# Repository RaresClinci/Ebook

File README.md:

# Openbook E-Reader

## Schema bloc
``` mermaid
 flowchart TB
    USB1["USB-C"] -->|5V| Charger1["Battery Charger (MCP73832)"]
    Charger1 -->|Charging| LiPo1["LiPo Battery"]
    LiPo1 --> LDO1["3V3 LDO"]
    LiPo1 --> DC5["5V DC/DC"]

    ESP1["ESP32-C3-WROOM"]

    LDO1 -->|3.3V| ESP1
    LDO1 -->|3.3V| Display1["1.5'' E-Ink Display (200x200px)"]
    LDO1 -->|3.3V| SD1["SD Card"]
    LDO1 -->|3.3V| Temp1["Temp/RH Sensor (BME680)"]
    LDO1 -->|3.3V| BatteryGauge["Battery Fuel Gauge (MAX17048)"]
    LDO1 -->|3.3V| Buttons1["Buttons (3x)"]

    ESP1 -- SPI --> Display1
    ESP1 -- SPI --> SD1
    ESP1 -- GPIO --> Buttons1
    ESP1 -- I2C --> Temp1
    ESP1 -- I2C --> BatteryGauge
    ESP1 -- I2C --> RTC["Real Time Clock (DS3231)"]
    ESP1 -- USB --> USB1

```

## Bill of Materials

Pentru componentele care se repeta, am adaugat doar la prima aparitioe datasheetul si linkul catre site.
TP-urile le-am proiectat singur, de aceea nu au o datasheet si un link catre site.

| Name of component  | Device                                    | Check Prices                                                                 | DataSheet                                                                  |
|--------------------|-------------------------------------------|-----------------------------------------------------------------------------|----------------------------------------------------------------------------|
| BOOT_BUTTON        | BUTTON_CUSYOMV1                           | [Check Price](https://industry.panasonic.com/global/en/products/control/switch/light-touch/number/evqpuj02k)  | [DataSheet](https://industry.panasonic.com/global/en/products/control/switch/light-touch/number/evqpuj02k) |
| C1                 | ESP32_WROVER_EAGLE-LTSPICE_CC0402         | [Check Price](https://industry.panasonic.com/global/en/products/control/switch/light-touch/number/evqpuj02k)  | [DataSheet](https://industry.panasonic.com/global/en/products/control/switch/light-touch/number/evqpuj02k) |
| C1_BAT             | ESP32_WROVER_EAGLE-LTSPICE_CC0402         | #N/A                                                                         | #N/A                                                                      |
| C1_BAT1            | EAGLE-LTSPICE_CC0402                      | #N/A                                                                         | #N/A                                                                      |
| C1_BAT2            | EAGLE-LTSPICE_CC0402                      | #N/A                                                                         | #N/A                                                                      |
| C2                 | ESP32_WROVER_EAGLE-LTSPICE_CC0402         | #N/A                                                                         | #N/A                                                                      |
| C2_BAT           | ESP32_WROVER_EAGLE-LTSPICE_CC0402         | #N/A                                                                         | #N/A                                                                      |
| C3                 | RCL_CPOL-EUCT3528                         | #N/A                                                                         | #N/A                                                                      |
| C4                 | ESP32_WROVER_EAGLE-LTSPICE_CC0402         | #N/A                                                                         | #N/A                                                                      |
| C4_USB             | ESP32_WROVER_EAGLE-LTSPICE_CC0402         | #N/A                                                                         | #N/A                                                                      |
| C5                 | ESP32_WROVER_EAGLE-LTSPICE_CC0402         | #N/A                                                                         | #N/A                                                                      |
| C5_USB             | ESP32_WROVER_EAGLE-LTSPICE_CC0402         | #N/A                                                                         | #N/A                                                                      |
| C6                 | ESP32_WROVER_EAGLE-LTSPICE_CC0402         | #N/A                                                                         | #N/A                                                                      |
| C7                 | ESP32_WROVER_EAGLE-LTSPICE_CC0402         | #N/A                                                                         | #N/A                                                                      |
| C8                 | ESP32_WROVER_EAGLE-LTSPICE_CC0402         | #N/A                                                                         | #N/A                                                                      |
| C9                 | EAGLE-LTSPICE_CC0402                      | #N/A                                                                         | #N/A                                                                      |
| C10                | ESP32_WROVER_EAGLE-LTSPICE_CC0402         | #N/A                                                                         | #N/A                                                                      |
| C10_SUPERCAP       | CPH3225A                                  | [Check Price](https://www.snapeda.com/parts/CPH3225A/Seiko+Instruments/view-part/?ref=eda) | [DataSheet](https://www.snapeda.com/parts/CPH3225A/Seiko+Instruments/view-part/?ref=eda) |
| CHANGE_BUTTON      | BUTTON_CUSYOMV1                           | [Check Price](https://industry.panasonic.com/global/en/products/control/switch-light-touch/number/evqpuj02k)  | [DataSheet](https://industry.panasonic.com/global/en/products/control/switch-light-touch/number/evqpuj02k) |
| CHG_LED            | ADAFRUIT_LEDCHIP-LED0603                  | [Check Price](https://www.snapeda.com/parts/KP-1608SURCK/Kingbright/view-part/?ref=search&t=LED%200603) | [DataSheet](https://www.snapeda.com/parts/KP-1608SURCK/Kingbright/view-part/?ref=search&t=LED%200603) |
| C_DELAY            | ESP32_WROVER_EAGLE-LTSPICE_CC0402         | #N/A                                                                         | #N/A                                                                      |
| D1                 | USBLC6-2SC6Y                              | [Check Price](https://www.snapeda.com/parts/USBLC6-2SC6Y/STMicroelectronics/view-part/?ref=eda) | [DataSheet](https://www.snapeda.com/parts/USBLC6-2SC6Y/STMicroelectronics/view-part/?ref=eda) |
| D2                 | ESP32_WROVER_AVX---SD0805S020S1R0_AVX_... | [Check Price](https://eu.mouser.com/ProductDetail/KYOCERA-AVX/SD0805S020S1R0?qs=jCA%252BPfw4LHbpkAoSnwrdjw%3D%3D) | [DataSheet](http://datasheets.avx.com/schottky.pdf)                       |
| D3                 | MBR0530                                   | [Check Price](https://eu.mouser.com/ProductDetail/KYOCERA-AVX/SD0805S020S1R0?qs=jCA%252BPfw4LHbpkAoSnwrdjw%3D%3D) | [DataSheet](https://eu.mouser.com/ProductDetail/KYOCERA-AVX/SD0805S020S1R0?qs=jCA%252BPfw4LHbpkAoSnwrdjw%3D%3D) |
| D4                 | MBR0530                                   | [Check Price](https://www.snapeda.com/parts/MBR0530/Onsemi/view-part/?ref=eda) | [DataSheet](https://www.snapeda.com/parts/MBR0530/Onsemi/view-part/?ref=eda) |
| D5                 | MBR0530                                   | [Check Price](https://www.snapeda.com/parts/MBR0530/Onsemi/view-part/?ref=eda) | [DataSheet](https://www.snapeda.com/parts/MBR0530/Onsemi/view-part/?ref=eda) |
| D6                 | PGB1010603MR                              | [Check Price](https://www.snapeda.com/parts/PGB1010603MR/Littelfuse/view-part/?ref=eda) | [DataSheet](https://www.snapeda.com/parts/PGB1010603MR/Littelfuse/view-part/?ref=eda) |
| D7                 | ESP32_WROVER_AVX---SD0805S020S1R0_AVX_... | [Check Price](https://eu.mouser.com/ProductDetail/KYOCERA-AVX/SD0805S020S1R0?qs=jCA%252BPfw4LHbpkAoSnwrdjw%3D%3D) | [DataSheet](http://datasheets.avx.com/schottky.pdf)                       |
| D8                 | PGB1010603MR                              | [Check Price](https://www.snapeda.com/parts/PGB1010603MR/Littelfuse/view-part/?ref=eda) | [DataSheet](https://www.snapeda.com/parts/PGB1010603MR/Littelfuse/view-part/?ref=eda) |
| D9                 | PGB1010603MR                              | [Check Price](https://www.snapeda.com/parts/PGB1010603MR/Littelfuse/view-part/?ref=eda) | [DataSheet](https://www.snapeda.com/parts/PGB1010603MR/Littelfuse/view-part/?ref=eda) |
| D10                | PGB1010603MR                              | [Check Price](https://www.snapeda.com/parts/PGB1010603MR/Littelfuse/view-part/?ref=eda) | [DataSheet](https://www.snapeda.com/parts/PGB1010603MR/Littelfuse/view-part/?ref=eda) |
| D11                | PGB1010603MR                              | [Check Price](https://www.snapeda.com/parts/PGB1010603MR/Littelfuse/view-part/?ref=eda) | [DataSheet](https://www.snapeda.com/parts/PGB1010603MR/Littelfuse/view-part/?ref=eda) |
| D12                | PGB1010603MR                              | [Check Price](https://www.snapeda.com/parts/PGB1010603MR/Littelfuse/view-part/?ref=eda) | [DataSheet](https://www.snapeda.com/parts/PGB1010603MR/Littelfuse/view-part/?ref=eda) |
| EPD_C1             | ESP32_WROVER_EAGLE-LTSPICE_CC0402         | #N/A                                                                         | #N/A                                                                      |
| EPD_C2             | ESP32_WROVER_EAGLE-LTSPICE_CC0402         | #N/A                                                                         | #N/A                                                                      |
| EPD_C5             | ESP32_WROVER_EAGLE-LTSPICE_CC0402         | #N/A                                                                         | #N/A                                                                      |
| EPD_C6             | ESP32_WROVER_EAGLE-LTSPICE_CC0402         | #N/A                                                                         | #N/A                                                                      |
| EPD_C7             | ESP32_WROVER_EAGLE-LTSPICE_CC0402         | #N/A                                                                         | #N/A                                                                      |
| EPD_C8             | ESP32_WROVER_EAGLE-LTSPICE_CC0402         | #N/A                                                                         | #N/A                                                                      |
| EPD_C9             | ESP32_WROVER_EAGLE-LTSPICE_CC0402         | #N/A                                                                         | #N/A                                                                      |
| EPD_C10            | ESP32_WROVER_EAGLE-LTSPICE_CC0402         | #N/A                                                                         | #N/A                                                                      |
| EPD_C11            | ESP32_WROVER_EAGLE-LTSPICE_CC0402         | #N/A                                                                         | #N/A                                                                      |
| EPD_C12            | ESP32_WROVER_EAGLE-LTSPICE_CC0402         | #N/A                                                                         | #N/A                                                                      |
| IC1                | BD5229G-TR                                | [Check Price](https://componentsearchengine.com/part-view/BD5229G-TR/ROHM%20Semiconductor) | [DataSheet](https://componentsearchengine.com/part-view/BD5229G-TR/ROHM%20Semiconductor) |
| IC4                | XC6220A331MR-G                            | [Check Price](https://componentsearchengine.com/part-view/XC6220A331MR-G/Torex) | [DataSheet](https://componentsearchengine.com/part-view/XC6220A331MR-G/Torex) |
| J1                 | FH34SRJ-24S-0.5SH_99_                     | [Check Price](https://componentsearchengine.com/part-view/XC6220A331MR-G/Torex) | [DataSheet](https://componentsearchengine.com/part-view/XC6220A331MR-G/Torex) |
| J2                 | SAMACSYS_PARTS_USB4110-GF-A               | [Check Price](https://componentsearchengine.com/part-view/USB4110-GF-A/GCT%20(GLOBAL%20CONNECTOR%20TECHNOLOGY) | [DataSheet](https://componentsearchengine.com/part-view/USB4110-GF-A/GCT%20(GLOBAL%20CONNECTOR%20TECHNOLOGY) |
| J3                 | QWIIC_CONNECTORJS-1MM                     | [Check Price](https://www.snapeda.com/parts/PRT-14417/SparkFun%20Electronics/view-part/?ref=search&t=qwiic%20connectpr)                                                                         | [Datasheet](https://www.snapeda.com/parts/PRT-14417/SparkFun%20Electronics/view-part/?ref=search&t=qwiic%20connectpr)                                                                        |
| J4                 | 112A-TAAR-R03_ATTEND                      | [Check Price](https://store.comet.srl.ro/Catalogue/Product/43497/)           | [DataSheet](https://store.comet.srl.ro/Catalogue/Product/43497/)          |
| L1                 | 744043680IND_4828-WE-TPC_WRE              | [Check Price](https://eu.mouser.com/ProductDetail/Wurth-Elektronik/744043680?qs=PGXP4M47uW6VkZq%252BkzjrHA%3D%3D) | [DataSheet](https://eu.mouser.com/ProductDetail/Wurth-Elektronik/744043680?qs=PGXP4M47uW6VkZq%252BkzjrHA%3D%3D) |
| PFMF.050.1         | ESP32C6_VARISTORCN1812                    | [Check Price](https://www.mouser.co.uk/ProductDetail/EPCOS-TDK/B72520T0350K062?qs=dEfas%2FXlABIszF52uu7vrg%3D%3D) | [DataSheet](https://www.mouser.co.uk/ProductDetail/EPCOS-TDK/B72520T0350K062?qs=dEfas%2FXlABIszF52uu7vrg%3D%3D) |
| Q1                 | ESP32_WROVER_SPARKFUN-DISCRETESEMI_MOSFET_... | [Check Price](https://componentsearchengine.com/part-view/DMG2305UX-7/Diodes%20Incorporated) | [DataSheet](https://componentsearchengine.com/part-view/DMG2305UX-7/Diodes%20Incorporated) |
| Q2                 | ESP32_WROVER_SPARKFUN-DISCRETESEMI_MOSFET_... | #N/A                                                                         | #N/A                                                                      |
| Q3                 | D8                                        | [Check Price](https://componentsearchengine.com/part-view/PGB1010603MR/Littelfuse) | [DataSheet](https://componentsearchengine.com/part-view/PGB1010603MR/Littelfuse) |
| Q4                 | Q2_TS-B2_REACHPACK                        | #N/A                                                                         | #N/A                                                                      |
| SJ1                 | SJ                                        | [Check Price](https://grabcad.com/library/solder-jumpers-1) | [DataSheet](https://grabcad.com/library/solder-jumpers-1) |                                                                  |

## Descriere detaliată a funcționalității hardware

### 1. Microcontroller – ESP32-C6
Dispozitivul se bazează pe microcontroller-ul**ESP32-C6-WROOM-1**, bazat pe un nucleu **RISC-V pe 32 de biți**, cu frecvențe de lucru de până la **160 MHz**.

- **Memorie**: 512 KB de SRAM intern și **8 MB flash extern** (W25Q512JVEIQ).
- **Conectivitate**: Wi-Fi 6, Bluetooth 5 LE, USB 2.0
- **Periferice**: suport pentru SPI, I²C, UART și multiple GPIO-uri.
- **Moduri de consum redus**: suportă sleep și deep sleep, ideale pentru dispozitive portabile alimentate cu baterie.

### 2. Afișaj E-Ink
**E-Ink de 7.5" (800x480px)** – Waveshare (sau echivalent) cu rezoluție 800×480

**Interfață**: 4-wire SPI + pini de control (CS, DC, RST, BUSY).  
**Consum**: extrem de redus în regim static; doar în timpul reîmprospătării imaginea consumul crește la ~15–25mA.

 **Avantaj**: Afișajele E-Ink păstrează imaginea fără consum de curent, ceea ce le face perfecte pentru aplicații de tip e-reader.

### 3. Senzor de Mediu – BME680
Senzorul integrează măsurători de **temperatură**, **umiditate**, **presiune atmosferică** și **calitate a aerului (VOC/eCO₂)**.

- **Interfață**: I²C la 400 kHz.
- **Consum**: ~2.1µA în standby, până la câțiva mA în timpul citirilor.

 **BME680** este o alegere excelenta datorita capacitatii sale de a integra multiple tipuri de masuratori intr-un singur cip

### 4. Managementul energiei
- **Baterie Li-Po 3.7V, 2500mAh** – oferă autonomie extinsă.
- **Circuit de încărcare**: MCP73831, conectat la USB-C, permite încărcare cu până la **1A**.
- **Fuel Gauge**: MAX17048 – monitorizează starea bateriei prin I²C (tensiune, încărcare, alertă descărcare).
- **LDO**: XC6220A331MR-G – asigură **tensiune stabilă de 3.3V** pentru toate componentele critice.

### 5. Interacțiune – Butoane (3x)
Dispozitivul include **trei butoane tactile** pentru navigare, selectare și întoarcere pagină. Fiecare este conectat la un GPIO și poate avea debouncing hardware (rezistor + condensator) sau software, pentru evitarea semnalelor false.

### 6. Port USB-C
- **Roluri**: încărcarea bateriei, transfer de date (USB 2.0), și update de firmware (via bootloader sau OTA).
- **Protecție**: ESD (ex: USBLC6-2SC6Y), rezistențe de terminare conforme cu specificațiile USB-C.

### 7. Conector Qwiic (I²C)
Conector standard cu 4 pini (VCC, GND, SDA, SCL) pentru atașarea rapidă a senzorilor/modulor I²C, ideal în extensii și prototipare.

### 8. Card MicroSD(112A-TAAR-R03)
- **Conector dedicat**: pentru log-uri, e-book-uri sau update-uri firmware.
- **Interfață**: Poate fi SD (1-bit / 4-bit) sau SPI, în funcție de configurația firmware-ului.

### 9. Ceas de timp real – RTC DS3231
- **Precizie ridicată**.
- **Backup**: cu baterie sau supercondensator.
- **Comunicare**: I²C, împreună cu ceilalți senzori.

### 10. Memorie Flash externă – W25Q512JVEIQ
- **Interfață**: quad SPI – pentru încărcare rapidă de date și firmware.
- Utilizată pentru stocarea aplicațiilor, imaginilor sau fișierelor mari (ex: e-book-uri).

---

### Interfețele utilizate

| Interfață | Componente conectate |
|----------|------------------------|
| **SPI**  | Afișaj E-Ink, memorie flash externă, card SD |
| **I²C**  | BME680, MAX17048 (fuel gauge), RTC DS3231, conector Qwiic |
| **GPIO** | Butoane, control display (RST, BUSY etc.) |
| **USB**  | Alimentare și date (USB-C) |

---

### Estimare consum energetic

| Componentă              | Consum tipic                     |
|-------------------------|----------------------------------|
| ESP32 (activ)           | ~80 mA (Wi-Fi) / <10 mA (idle)   |
| E-Ink (refresh)         | ~15–25 mA                        |
| BME680                  | ~3.6 mA (peak) / 2.1 µA (sleep)  |
| MAX17048 (Fuel Gauge)   | ~50 µA                           |
| DS3231 (RTC)            | ~3.5 mA (activ) / <1 µA (backup) |
| Total (deep sleep)      | ~50–100 µA                       |
| Total (activ cu Wi-Fi)  | ~100–150 mA                      |

> Cu o baterie de **2500mAh**, în regim normal de utilizare (afișaj static, deep sleep majoritatea timpului), autonomia poate atinge **câteva săptămâni**.

## Alocarea pinilor pentru ESP32-C6

| Pin ESP32-C6  | Componentă / Semnal                       | Descriere                                           |
|---------------|-------------------------------------------|-----------------------------------------------------|
| GPIO1         | I²C SDA (BME680, MAX17048, DS3231, Qwiic) | Linie de date partajată pentru toți senzorii(+ RTC) conectați pe magistrala I²C. |
| GPIO2         | I²C SCL (BME680, MAX17048, DS3231, Qwiic) | Linie de clock pentru sincronizarea comunicației I²C. |
| GPIO5         | SPI MISO (E-Paper)                        | Recepție date de la afișajul E-Paper.              |
| GPIO6         | SPI MOSI (E-Paper)                        | Transmitere date către afișajul E-Paper.           |
| GPIO7         | SPI CLK (E-Paper)                         | Semnal de clock pentru interfața SPI a ecranului.  |
| GPIO8         | SPI CS (E-Paper)                          | Chip Select pentru e-paper.   |
| GPIO9         | E-Paper DC (Data/Command)                 | Selectează între transmiterea de date sau comenzi către afișaj. |
| GPIO10        | E-Paper RST                               | Reset hardware al afișajului.                      |
| GPIO11        | E-Paper BUSY                              | Indică dacă afișajul este ocupat cu o operație.    |
| GPIO12        | Button #1                                 | Buton de control (ex. „Pagina următoare”).         |
| GPIO13        | Button #2                                 | Buton de control (ex. „Pagina anterioară”).        |
| GPIO14        | Button #3                                 | Buton de control (ex. „Meniu” sau „Select”).       |
| GPIO15        | MAX17048 ALERT (opțional)                 | Semnal de alertă de la senzorul de baterie (low battery). |
| GPIO16        | USB D+ (intern la USB PHY)                | Semnal diferențial pozitiv pentru conexiunea USB 2.0. |
| GPIO17        | USB D- (intern la USB PHY)                | Semnal diferențial negativ pentru conexiunea USB 2.0. |
| GPIO18        | LED de status (opțional)                  | LED pentru semnalizare stări (Wi-Fi, încărcare etc.). |
| GPIO19        | SD Card CS (opțional)                     | Chip Select pentru cardul microSD (SPI).           |
| GPIO20        | SD Card MISO (opțional)                   | Linie de citire date de la cardul microSD.         |
| GPIO21        | SD Card MOSI (opțional)                   | Linie de scriere date către cardul microSD.        |
| GPIO4         | SD Card CLK (opțional)                    | Linie de clock pentru comunicația SPI cu cardul SD.|

## Note
- am adaugat la partea de PCB 2D niste masuratori in plus pentru claritate
- am pozitionat TP-urile in cel mai apropiat loc de componentele conectate
- am mai adaugat pe placa o zona unde poate fi scris numarul de serie al placii si versiunea ei(probabil va deveni Openbook v1.2 dupa feedback - UPDATE: chiar a devenit)
- pentru baterie, am folosit un paralelipiped cu dimensiunile maxime din datasheet
- la partea de PCB, am aprobat 2 erori de gauri de la o componenta si o eroare de Airwire la componenta J4, are 9 grounduri puse intr-un grid 3x3 si cel din mijloc nu e accesibil

## Concluzii
A fost un proiect destul de solicitant, dar cu multa munca am reusit sa il duc pana la capat. Am luat in considerare majoritatea indicatiilor si sunt deschis sa fac imbunatatiri pe urma feedbackului.

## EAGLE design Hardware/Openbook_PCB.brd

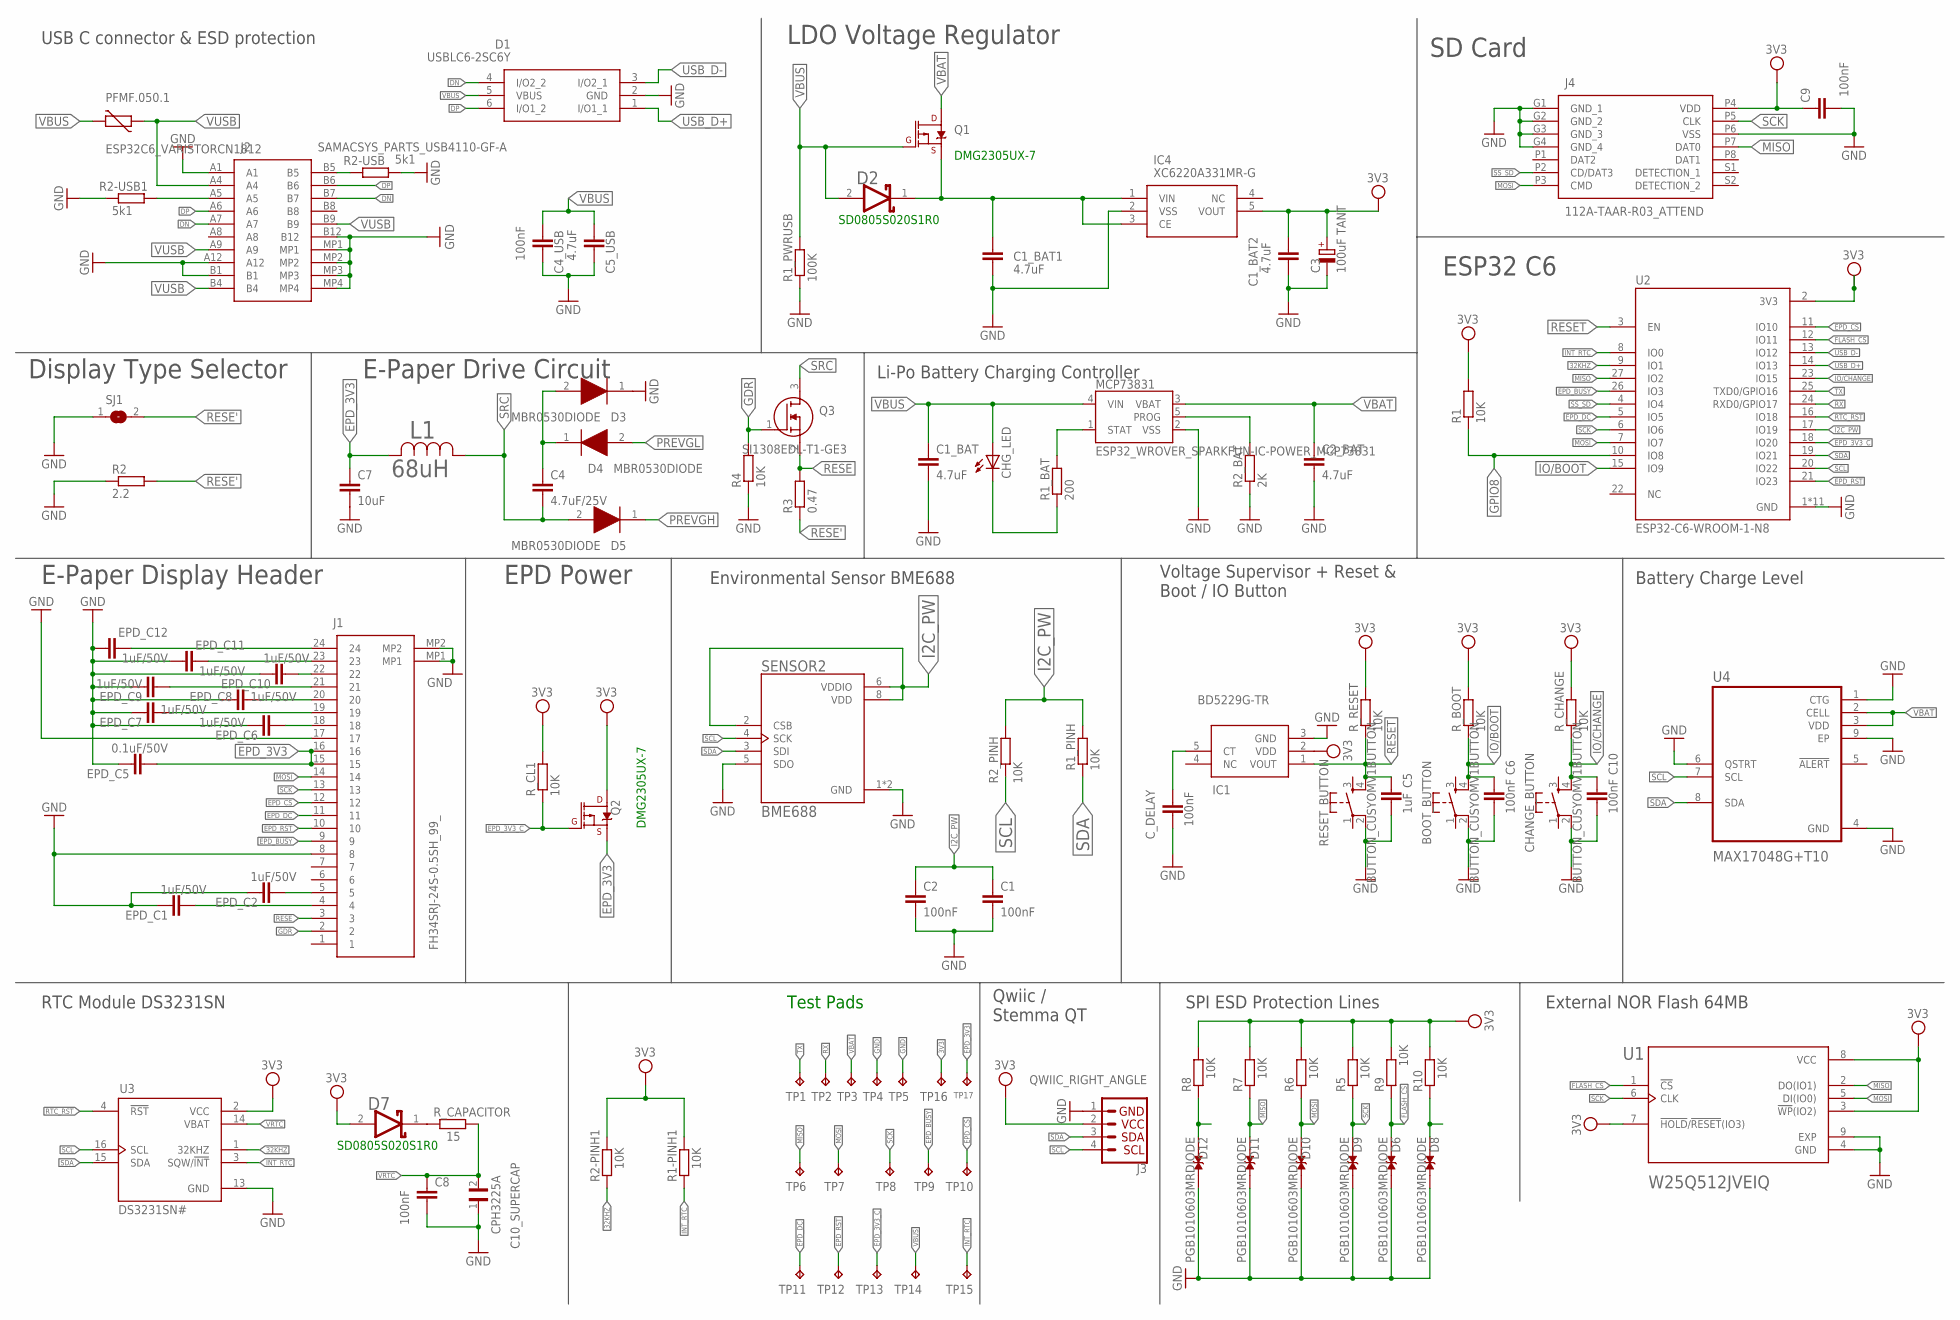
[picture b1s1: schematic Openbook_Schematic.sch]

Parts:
BOOT_BUTTON: BUTTON_CUSYOMV1BUTTON; MYBUTTON
C1, C2, C4_USB, C6, C8, C9, C10: 100nF; EAGLE-LTSPICE_C0402
C1_BAT, C1_BAT1, C1_BAT2, C2_BAT, C5_USB: 4.7uF; EAGLE-LTSPICE_C0402
C3: 100uF TANT; RCL_CT3528
C4: 4.7uF/25V; EAGLE-LTSPICE_C0402
C5: 1uF; EAGLE-LTSPICE_C0402
C7: 10uF; EAGLE-LTSPICE_C0402
C10_SUPERCAP: CPH3225A; CAPCP3225X100N
CHANGE_BUTTON: BUTTON_CUSYOMV1BUTTON; MYBUTTON
CHG_LED: ADAFRUIT_LEDCHIP-LED0603; ADAFRUIT_CHIP-LED0603
C_DELAY: 100nF; EAGLE-LTSPICE_C0402
D1: USBLC6-2SC6Y; SOT95P280X145-6N
D2, D7: SD0805S020S1R0; ESP32_WROVER_AVX---SD0805S020S1R0_AVX_SD0805S020S1R0_0
D3, D4, D5: MBR0530DIODE; SOD3716X135N
D6, D8, D9, D10, D11, D12: PGB1010603MRDIODE; DIOC1608X36N
EPD_C1, EPD_C2, EPD_C6, EPD_C7, EPD_C8, EPD_C9, EPD_C10, EPD_C11, EPD_C12: 1uF/50V; EAGLE-LTSPICE_C0402
EPD_C5: 0.1uF/50V; EAGLE-LTSPICE_C0402
IC1: BD5229G-TR; SOT95P280X125-5N
IC4: XC6220A331MR-G; SOT95P280X120-5N
J1: FH34SRJ-24S-0.5SH_99_; FH34SRJ24S05SH99
J2: SAMACSYS_PARTS_USB4110-GF-A; SAMACSYS_PARTS_USB4110GFA
J3: QWIIC_RIGHT_ANGLE; JST04_1MM_RA
J4: 112A-TAAR-R03_ATTEND; 112ATAARR03ATTEND
L1: 68uH; IND_4828-WE-TPC_WRE
MCP73831: ESP32_WROVER_SPARKFUN-IC-POWER_MCP73831; ESP32_WROVER_SPARKFUN-IC-POWER_SOT23-5
PFMF.050.1: ESP32C6_VARISTORCN1812; ESP32C6_VARISTOR_CT/CN1812
Q1, Q2: 20V/4.2A/52mΩ/1.4W; ESP32_WROVER_SPARKFUN-DISCRETESEMI_SOT23-3
Q3: SI1308EDL-T1-GE3; SOT65P210X110-3N
R1, R1-PINH1, R1_PINH, R2-PINH1, R2_PINH, R4, R5, R6, R7, R8, R9, R10: 10K; ESP32_WROVER_EAGLE-LTSPICE_R0402
R1_BAT: 200; ESP32_WROVER_EAGLE-LTSPICE_R0402
R1_PWRUSB: 100K; ESP32_WROVER_EAGLE-LTSPICE_R0402
R2: 2.2; ESP32_WROVER_EAGLE-LTSPICE_R0402
R2-USB, R2-USB1: 5k1; ESP32_WROVER_EAGLE-LTSPICE_R0402
R2_BAT: 2K; ESP32_WROVER_EAGLE-LTSPICE_R0402
R3: 0.47; ESP32_WROVER_EAGLE-LTSPICE_R0402
RESET_BUTTON: BUTTON_CUSYOMV1BUTTON; MYBUTTON
R_BOOT: 10K; ESP32_WROVER_EAGLE-LTSPICE_R0402
R_CAPACITOR: 15; ESP32_WROVER_EAGLE-LTSPICE_R0402
R_CHANGE: 10K; ESP32_WROVER_EAGLE-LTSPICE_R0402
R_CL1: 10K; ESP32_WROVER_EAGLE-LTSPICE_R0402
R_RESET: 10K; ESP32_WROVER_EAGLE-LTSPICE_R0402
SENSOR2: BME688; ESP32_WROVER_BME680_PSON80P300X300X100-8N
SJ1: SJ
TP1, TP2, TP3, TP4, TP5, TP6, TP7, TP8, TP9, TP10, TP11, TP12, TP13, TP14, TP15, TP16, TP17: TPTP20R; TP20R
U1: W25Q512JVEIQ; SON127P600X800X80-9N
U2: ESP32-C6-WROOM-1-N8; XCVR_ESP32-C6-WROOM-1-N8
U3: DS3231SN#; SOIC127P1032X265-16N
U4: MAX17048G+T10; SON50P200X200X80-9N

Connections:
3V3: C1_BAT2.1, C3.+, C9.1, D7.2 (ANODE), IC1.2 (VDD), IC4.5 (VOUT), J3.2, J4.P4 (VDD), Q2.3 (D), R1.2, R1-PINH1.2, R2-PINH1.2, R5.2, R6.2, R7.2, R8.2, R9.2, R10.2, R_BOOT.2, R_CHANGE.2, R_CL1.2, R_RESET.2, TP16.TP, U1.3 (!WP!(IO2)), U1.7 (!HOLD!/!RESET!(IO3)), U1.8 (VCC), U2.2 (3V3), U3.2 (VCC)
32KHZ: R2-PINH1.1, U2.9 (IO1), U3.1 (32KHZ)
DN: D1.4 (I/O2_2), J2.A7, J2.B7
DP: D1.6 (I/O1_2), J2.A6, J2.B6
EPD_3V3: C7.1, EPD_C5.2, J1.15, J1.16, L1.2, Q2.2 (S), TP17.TP
EPD_3V3_C: Q2.1 (G), R_CL1.1, TP13.TP, U2.18 (IO20)
EPD_BUSY: J1.9, TP9.TP, U2.26 (IO3)
EPD_CS: J1.12, TP10.TP, U2.11 (IO10)
EPD_DC: J1.11, TP11.TP, U2.5 (IO5)
EPD_RST: J1.10, TP12.TP, U2.21 (IO23)
FLASH_CS: D6.1, R9.1, U1.1 (!CS), U2.12 (IO11)
GDR: J1.2, Q3.1 (G), R4.2
GND: BOOT_BUTTON.2, C1.2, C1_BAT.2, C1_BAT1.2, C1_BAT2.2, C2.2, C2_BAT.2, C3.-, C4_USB.2, C5.2, C5_USB.2, C6.2, C7.2, C8.2, C9.2, C10.2, C10_SUPERCAP.1, CHANGE_BUTTON.2, C_DELAY.2, D1.2 (GND), D3.1 (K), D6.2, D8.2, D9.2, D10.2, D11.2, D12.2, EPD_C1.1, EPD_C2.1, EPD_C5.1, EPD_C6.1, EPD_C7.1, EPD_C8.1, EPD_C9.1, EPD_C10.1, EPD_C11.1, EPD_C12.1, IC1.3 (GND), IC4.2 (VSS), J1.8, J1.17, J1.MP1, J1.MP2, J2.A1, J2.A12, J2.B1, J2.B12, J2.MP1, J2.MP2, J2.MP3, J2.MP4, J3.1, J4.G1 (GND_1), J4.G2 (GND_2), J4.G3 (GND_3), J4.G4 (GND_4), J4.P6 (VSS), MCP73831.2 (VSS), R1_PWRUSB.1, R2.1, R2-USB.2, R2-USB1.1, R2_BAT.1, R4.1, RESET_BUTTON.2, SENSOR2.1 (GND), SENSOR2.5 (SDO), SENSOR2.7 (GND), SJ1.1, TP4.TP, TP5.TP, U1.4 (GND), U1.9 (EXP), U2.1 (GND), U2.28 (GND), U2.29_1 (GND), U2.29_2 (GND), U2.29_3 (GND), U2.29_4 (GND), U2.29_5 (GND), U2.29_6 (GND), U2.29_7 (GND), U2.29_8 (GND), U2.29_9 (GND), U3.13 (GND), U4.1 (CTG), U4.4 (GND), U4.6 (QSTRT), U4.9 (EP)
GPIO8: R1.1, U2.10 (IO8)
I2C_PW: C1.1, C2.1, R1_PINH.2, R2_PINH.2, SENSOR2.2 (CSB), SENSOR2.6 (VDDIO), SENSOR2.8 (VDD), U2.17 (IO19)
INT_RTC: R1-PINH1.1, TP15.TP, U2.8 (IO0), U3.3 (SQW/!INT)
IO/BOOT: BOOT_BUTTON.4, C6.1, R_BOOT.1, U2.15 (IO9)
IO/CHANGE: C10.1, CHANGE_BUTTON.4, R_CHANGE.1, U2.23 (IO15)
MISO: D11.1, J4.P7 (DAT0), R7.1, TP6.TP, U1.2 (DO(IO1)), U2.27 (IO2)
MOSI: D10.1, J1.14, J4.P3 (CMD), R6.1, TP7.TP, U1.5 (DI(IO0)), U2.7 (IO7)
unnamed: J2.A5, R2-USB1.2
unnamed: J2.B5, R2-USB.1
unnamed: C1_BAT1.1, D2.1 (CATHODE), IC4.1 (VIN), IC4.3 (CE), Q1.2 (S)
unnamed: EPD_C12.2, J1.24
unnamed: C4.1, D3.2 (A), D4.1 (K)
unnamed: MCP73831.5 (PROG), R2_BAT.2
unnamed: CHG_LED.C, R1_BAT.1
unnamed: MCP73831.1 (STAT), R1_BAT.2
unnamed: EPD_C11.2, J1.23
unnamed: EPD_C10.2, J1.22
unnamed: EPD_C9.2, J1.21
unnamed: EPD_C8.2, J1.20
unnamed: EPD_C7.2, J1.19
unnamed: EPD_C6.2, J1.18
unnamed: EPD_C2.2, J1.5
unnamed: EPD_C1.2, J1.4
unnamed: C_DELAY.1, IC1.5 (CT)
unnamed: D7.1 (CATHODE), R_CAPACITOR.1
unnamed: D12.1, R8.1
PREVGH: D5.1 (K)
PREVGL: D4.2 (A)
RESE: J1.3, Q3.2 (S), R3.2
RESE': R2.2, R3.1, SJ1.2
RESET: C5.1, IC1.1 (VOUT), RESET_BUTTON.4, R_RESET.1, U2.3 (EN)
RTC_RST: U2.16 (IO18), U3.4 (!RST)
RX: TP2.TP, U2.24 (RXD0/GPIO17)
SCK: D9.1, J1.13, J4.P5 (CLK), R5.1, TP8.TP, U1.6 (CLK), U2.6 (IO6)
SCL: J3.4, R2_PINH.1, SENSOR2.4 (SCK), U2.20 (IO22), U3.16 (SCL), U4.7 (SCL)
SDA: J3.3, R1_PINH.1, SENSOR2.3 (SDI), U2.19 (IO21), U3.15 (SDA), U4.8 (SDA)
SRC: C4.2, D5.2 (A), L1.1, Q3.3 (D)
SS_SD: J4.P2 (CD/DAT3), U2.4 (IO4)
SS_SD1: D8.1, R10.1
TX: TP1.TP, U2.25 (TXD0/GPIO16)
USB_D+: D1.1 (I/O1_1), U2.14 (IO13)
USB_D-: D1.3 (I/O2_1), U2.13 (IO12)
VBAT: C2_BAT.1, MCP73831.3 (VBAT), Q1.3 (D), TP3.TP, U4.2 (CELL), U4.3 (VDD)
VBUS: C1_BAT.1, C4_USB.1, C5_USB.1, CHG_LED.A, D1.5 (VBUS), D2.2 (ANODE), MCP73831.4 (VIN), PFMF.050.1.2, Q1.1 (G), R1_PWRUSB.2, TP14.TP
VRTC: C8.1, C10_SUPERCAP.2, R_CAPACITOR.2, U3.14 (VBAT)
VUSB: J2.A4, J2.A9, J2.B4, J2.B9, PFMF.050.1.1

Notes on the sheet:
USB C connector & ESD protection
DMG2305UX-7
SD0805S020S1R0
LDO Voltage Regulator
SD Card
Display Type Selector
E-Paper Drive Circuit
Li-Po Battery Charging Controller
ESP32 C6
E-Paper Display Header
EPD Power
Environmental Sensor BME688
Voltage Supervisor + Reset & Boot / IO Button
Battery Charge Level
RTC Module DS3231SN
Test Pads
SPI ESD Protection Lines
External NOR Flash 64MB
Qwiic / Stemma QT

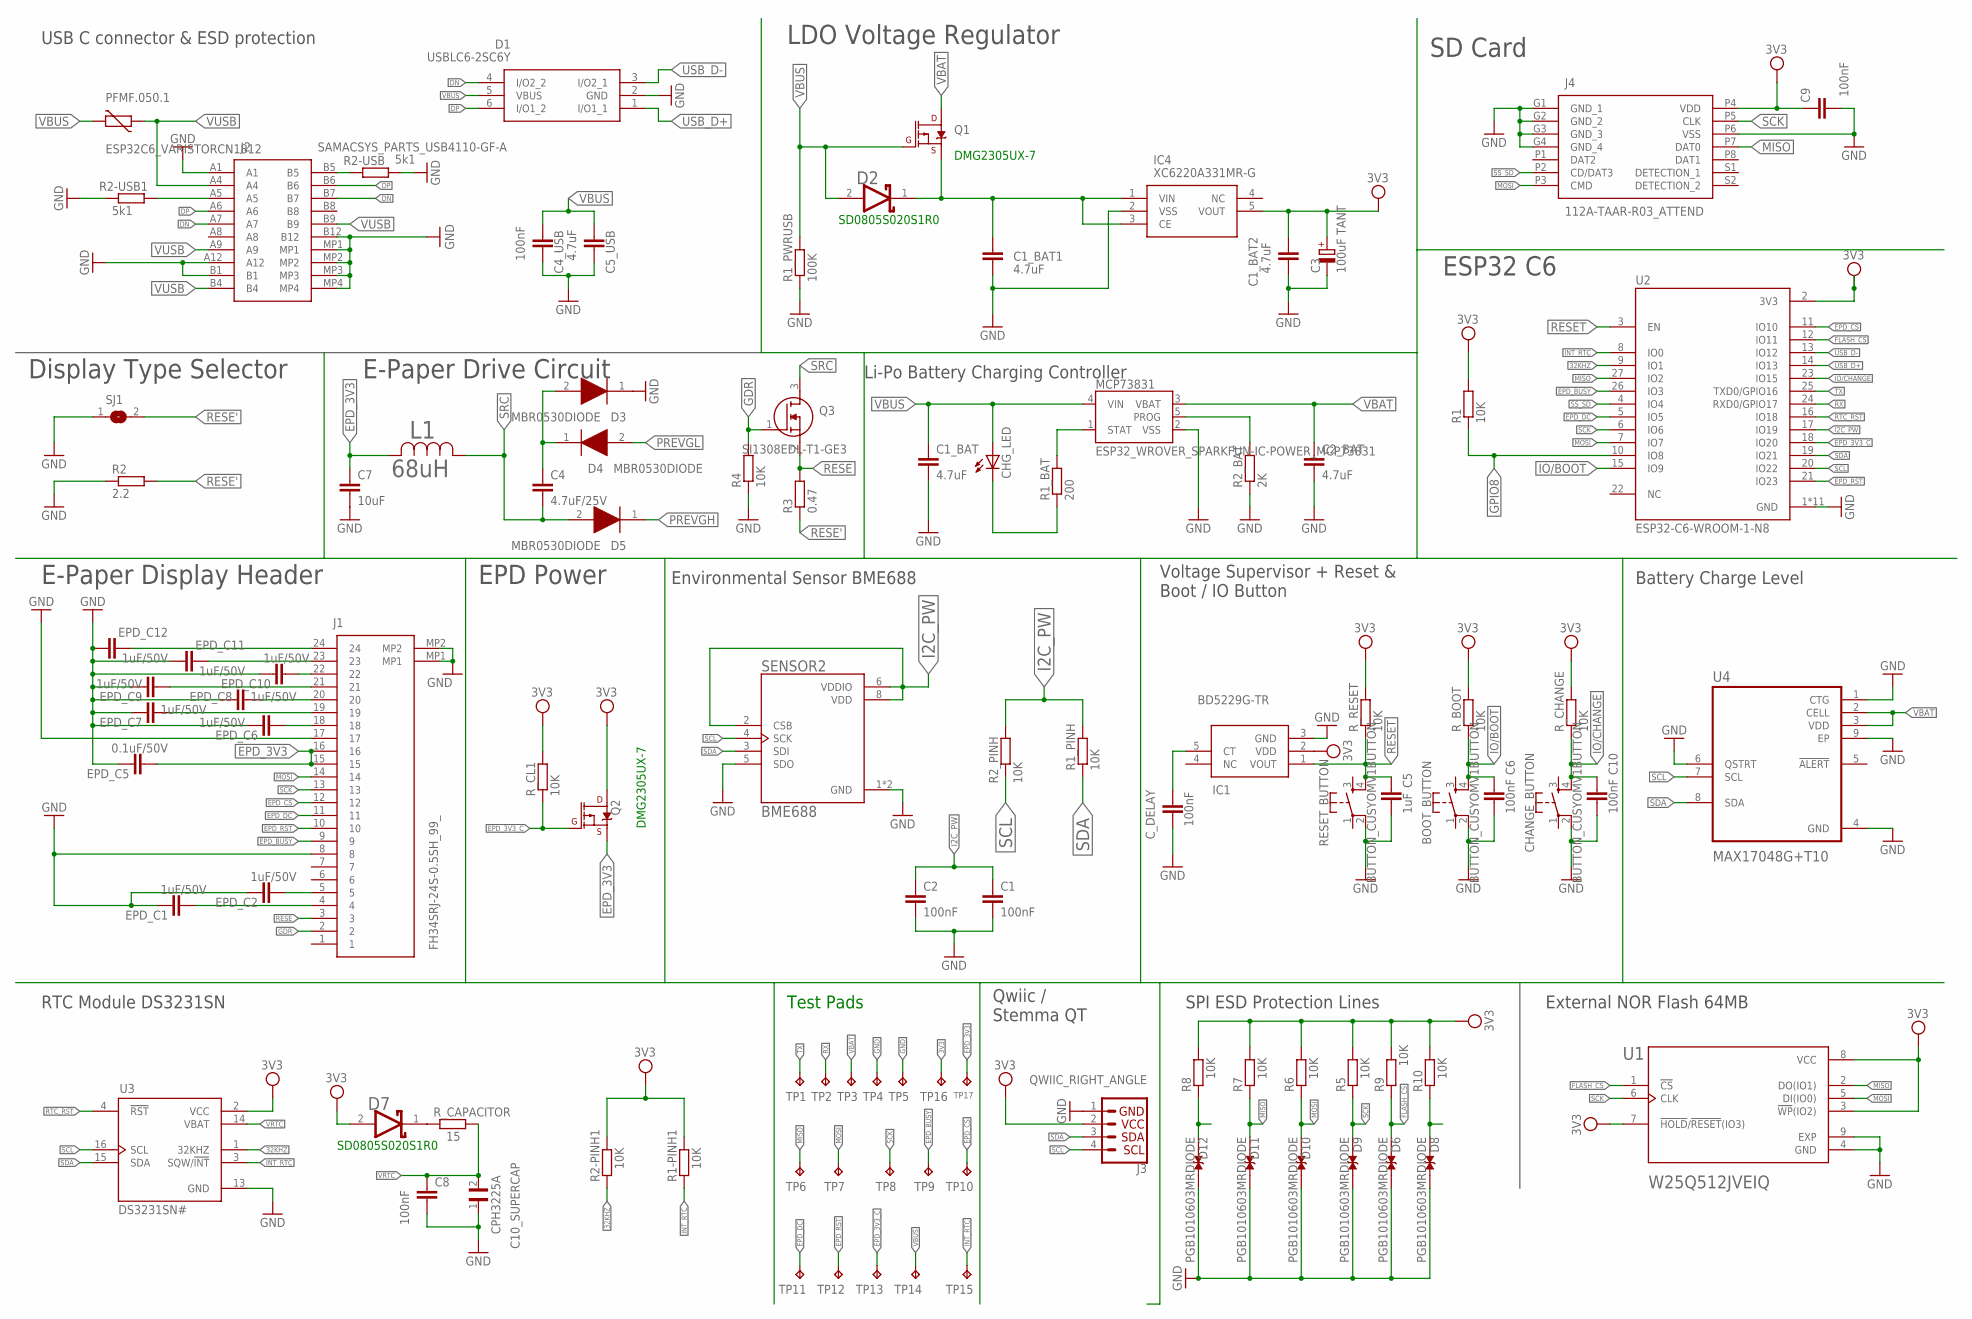
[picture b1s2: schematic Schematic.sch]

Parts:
BOOT_BUTTON: BUTTON_CUSYOMV1BUTTON; MYBUTTON
C1, C2, C4_USB, C6, C8, C9, C10: 100nF; EAGLE-LTSPICE_C0402
C1_BAT, C1_BAT1, C1_BAT2, C2_BAT, C5_USB: 4.7uF; EAGLE-LTSPICE_C0402
C3: 100uF TANT; RCL_CT3528
C4: 4.7uF/25V; EAGLE-LTSPICE_C0402
C5: 1uF; EAGLE-LTSPICE_C0402
C7: 10uF; EAGLE-LTSPICE_C0402
C10_SUPERCAP: CPH3225A; CAPCP3225X100N
CHANGE_BUTTON: BUTTON_CUSYOMV1BUTTON; MYBUTTON
CHG_LED: ADAFRUIT_LEDCHIP-LED0603; ADAFRUIT_CHIP-LED0603
C_DELAY: 100nF; EAGLE-LTSPICE_C0402
D1: USBLC6-2SC6Y; SOT95P280X145-6N
D2, D7: SD0805S020S1R0; ESP32_WROVER_AVX---SD0805S020S1R0_AVX_SD0805S020S1R0_0
D3, D4, D5: MBR0530DIODE; SOD3716X135N
D6, D8, D9, D10, D11, D12: PGB1010603MRDIODE; DIOC1608X36N
EPD_C1, EPD_C2, EPD_C6, EPD_C7, EPD_C8, EPD_C9, EPD_C10, EPD_C11, EPD_C12: 1uF/50V; EAGLE-LTSPICE_C0402
EPD_C5: 0.1uF/50V; EAGLE-LTSPICE_C0402
IC1: BD5229G-TR; SOT95P280X125-5N
IC4: XC6220A331MR-G; SOT95P280X120-5N
J1: FH34SRJ-24S-0.5SH_99_; FH34SRJ24S05SH99
J2: SAMACSYS_PARTS_USB4110-GF-A; SAMACSYS_PARTS_USB4110GFA
J3: QWIIC_RIGHT_ANGLE; JST04_1MM_RA
J4: 112A-TAAR-R03_ATTEND; 112ATAARR03ATTEND
L1: 68uH; IND_4828-WE-TPC_WRE
MCP73831: ESP32_WROVER_SPARKFUN-IC-POWER_MCP73831; ESP32_WROVER_SPARKFUN-IC-POWER_SOT23-5
PFMF.050.1: ESP32C6_VARISTORCN1812; ESP32C6_VARISTOR_CT/CN1812
Q1, Q2: 20V/4.2A/52mΩ/1.4W; ESP32_WROVER_SPARKFUN-DISCRETESEMI_SOT23-3
Q3: SI1308EDL-T1-GE3; SOT65P210X110-3N
R1, R1-PINH1, R1_PINH, R2-PINH1, R2_PINH, R4, R5, R6, R7, R8, R9, R10: 10K; ESP32_WROVER_EAGLE-LTSPICE_R0402
R1_BAT: 200; ESP32_WROVER_EAGLE-LTSPICE_R0402
R1_PWRUSB: 100K; ESP32_WROVER_EAGLE-LTSPICE_R0402
R2: 2.2; ESP32_WROVER_EAGLE-LTSPICE_R0402
R2-USB, R2-USB1: 5k1; ESP32_WROVER_EAGLE-LTSPICE_R0402
R2_BAT: 2K; ESP32_WROVER_EAGLE-LTSPICE_R0402
R3: 0.47; ESP32_WROVER_EAGLE-LTSPICE_R0402
RESET_BUTTON: BUTTON_CUSYOMV1BUTTON; MYBUTTON
R_BOOT: 10K; ESP32_WROVER_EAGLE-LTSPICE_R0402
R_CAPACITOR: 15; ESP32_WROVER_EAGLE-LTSPICE_R0402
R_CHANGE: 10K; ESP32_WROVER_EAGLE-LTSPICE_R0402
R_CL1: 10K; ESP32_WROVER_EAGLE-LTSPICE_R0402
R_RESET: 10K; ESP32_WROVER_EAGLE-LTSPICE_R0402
SENSOR2: BME688; ESP32_WROVER_BME680_PSON80P300X300X100-8N
SJ1: SJ
TP1, TP2, TP3, TP4, TP5, TP6, TP7, TP8, TP9, TP10, TP11, TP12, TP13, TP14, TP15, TP16, TP17: TPTP20R; TP20R
U1: W25Q512JVEIQ; SON127P600X800X80-9N
U2: ESP32-C6-WROOM-1-N8; XCVR_ESP32-C6-WROOM-1-N8
U3: DS3231SN#; SOIC127P1032X265-16N
U4: MAX17048G+T10; SON50P200X200X80-9N

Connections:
3V3: C1_BAT2.1, C3.+, C9.1, D7.2 (ANODE), IC1.2 (VDD), IC4.5 (VOUT), J3.2, J4.P4 (VDD), Q2.3 (D), R1.2, R1-PINH1.2, R2-PINH1.2, R5.2, R6.2, R7.2, R8.2, R9.2, R10.2, R_BOOT.2, R_CHANGE.2, R_CL1.2, R_RESET.2, TP16.TP, U1.3 (!WP!(IO2)), U1.7 (!HOLD!/!RESET!(IO3)), U1.8 (VCC), U2.2 (3V3), U3.2 (VCC)
32KHZ: R2-PINH1.1, U2.9 (IO1), U3.1 (32KHZ)
DN: D1.4 (I/O2_2), J2.A7, J2.B7
DP: D1.6 (I/O1_2), J2.A6, J2.B6
EPD_3V3: C7.1, EPD_C5.2, J1.15, J1.16, L1.2, Q2.2 (S), TP17.TP
EPD_3V3_C: Q2.1 (G), R_CL1.1, TP13.TP, U2.18 (IO20)
EPD_BUSY: J1.9, TP9.TP, U2.26 (IO3)
EPD_CS: J1.12, TP10.TP, U2.11 (IO10)
EPD_DC: J1.11, TP11.TP, U2.5 (IO5)
EPD_RST: J1.10, TP12.TP, U2.21 (IO23)
FLASH_CS: D6.1, R9.1, U1.1 (!CS), U2.12 (IO11)
GDR: J1.2, Q3.1 (G), R4.2
GND: BOOT_BUTTON.2, C1.2, C1_BAT.2, C1_BAT1.2, C1_BAT2.2, C2.2, C2_BAT.2, C3.-, C4_USB.2, C5.2, C5_USB.2, C6.2, C7.2, C8.2, C9.2, C10.2, C10_SUPERCAP.1, CHANGE_BUTTON.2, C_DELAY.2, D1.2 (GND), D3.1 (K), D6.2, D8.2, D9.2, D10.2, D11.2, D12.2, EPD_C1.1, EPD_C2.1, EPD_C5.1, EPD_C6.1, EPD_C7.1, EPD_C8.1, EPD_C9.1, EPD_C10.1, EPD_C11.1, EPD_C12.1, IC1.3 (GND), IC4.2 (VSS), J1.8, J1.17, J1.MP1, J1.MP2, J2.A1, J2.A12, J2.B1, J2.B12, J2.MP1, J2.MP2, J2.MP3, J2.MP4, J3.1, J4.G1 (GND_1), J4.G2 (GND_2), J4.G3 (GND_3), J4.G4 (GND_4), J4.P6 (VSS), MCP73831.2 (VSS), R1_PWRUSB.1, R2.1, R2-USB.2, R2-USB1.1, R2_BAT.1, R4.1, RESET_BUTTON.2, SENSOR2.1 (GND), SENSOR2.5 (SDO), SENSOR2.7 (GND), SJ1.1, TP4.TP, TP5.TP, U1.4 (GND), U1.9 (EXP), U2.1 (GND), U2.28 (GND), U2.29_1 (GND), U2.29_2 (GND), U2.29_3 (GND), U2.29_4 (GND), U2.29_5 (GND), U2.29_6 (GND), U2.29_7 (GND), U2.29_8 (GND), U2.29_9 (GND), U3.13 (GND), U4.1 (CTG), U4.4 (GND), U4.6 (QSTRT), U4.9 (EP)
GPIO8: R1.1, U2.10 (IO8)
I2C_PW: C1.1, C2.1, R1_PINH.2, R2_PINH.2, SENSOR2.2 (CSB), SENSOR2.6 (VDDIO), SENSOR2.8 (VDD), U2.17 (IO19)
INT_RTC: R1-PINH1.1, TP15.TP, U2.8 (IO0), U3.3 (SQW/!INT)
IO/BOOT: BOOT_BUTTON.4, C6.1, R_BOOT.1, U2.15 (IO9)
IO/CHANGE: C10.1, CHANGE_BUTTON.4, R_CHANGE.1, U2.23 (IO15)
MISO: D11.1, J4.P7 (DAT0), R7.1, TP6.TP, U1.2 (DO(IO1)), U2.27 (IO2)
MOSI: D10.1, J1.14, J4.P3 (CMD), R6.1, TP7.TP, U1.5 (DI(IO0)), U2.7 (IO7)
unnamed: J2.A5, R2-USB1.2
unnamed: J2.B5, R2-USB.1
unnamed: C1_BAT1.1, D2.1 (CATHODE), IC4.1 (VIN), IC4.3 (CE), Q1.2 (S)
unnamed: EPD_C12.2, J1.24
unnamed: C4.1, D3.2 (A), D4.1 (K)
unnamed: MCP73831.5 (PROG), R2_BAT.2
unnamed: CHG_LED.C, R1_BAT.1
unnamed: MCP73831.1 (STAT), R1_BAT.2
unnamed: EPD_C11.2, J1.23
unnamed: EPD_C10.2, J1.22
unnamed: EPD_C9.2, J1.21
unnamed: EPD_C8.2, J1.20
unnamed: EPD_C7.2, J1.19
unnamed: EPD_C6.2, J1.18
unnamed: EPD_C2.2, J1.5
unnamed: EPD_C1.2, J1.4
unnamed: C_DELAY.1, IC1.5 (CT)
unnamed: D7.1 (CATHODE), R_CAPACITOR.1
unnamed: D12.1, R8.1
PREVGH: D5.1 (K)
PREVGL: D4.2 (A)
RESE: J1.3, Q3.2 (S), R3.2
RESE': R2.2, R3.1, SJ1.2
RESET: C5.1, IC1.1 (VOUT), RESET_BUTTON.4, R_RESET.1, U2.3 (EN)
RTC_RST: U2.16 (IO18), U3.4 (!RST)
RX: TP2.TP, U2.24 (RXD0/GPIO17)
SCK: D9.1, J1.13, J4.P5 (CLK), R5.1, TP8.TP, U1.6 (CLK), U2.6 (IO6)
SCL: J3.4, R2_PINH.1, SENSOR2.4 (SCK), U2.20 (IO22), U3.16 (SCL), U4.7 (SCL)
SDA: J3.3, R1_PINH.1, SENSOR2.3 (SDI), U2.19 (IO21), U3.15 (SDA), U4.8 (SDA)
SRC: C4.2, D5.2 (A), L1.1, Q3.3 (D)
SS_SD: J4.P2 (CD/DAT3), U2.4 (IO4)
SS_SD1: D8.1, R10.1
TX: TP1.TP, U2.25 (TXD0/GPIO16)
USB_D+: D1.1 (I/O1_1), U2.14 (IO13)
USB_D-: D1.3 (I/O2_1), U2.13 (IO12)
VBAT: C2_BAT.1, MCP73831.3 (VBAT), Q1.3 (D), TP3.TP, U4.2 (CELL), U4.3 (VDD)
VBUS: C1_BAT.1, C4_USB.1, C5_USB.1, CHG_LED.A, D1.5 (VBUS), D2.2 (ANODE), MCP73831.4 (VIN), PFMF.050.1.2, Q1.1 (G), R1_PWRUSB.2, TP14.TP
VRTC: C8.1, C10_SUPERCAP.2, R_CAPACITOR.2, U3.14 (VBAT)
VUSB: J2.A4, J2.A9, J2.B4, J2.B9, PFMF.050.1.1

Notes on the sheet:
USB C connector & ESD protection
DMG2305UX-7
SD0805S020S1R0
LDO Voltage Regulator
SD Card
Display Type Selector
E-Paper Drive Circuit
Li-Po Battery Charging Controller
ESP32 C6
E-Paper Display Header
EPD Power
Environmental Sensor BME688
Voltage Supervisor + Reset & Boot / IO Button
Battery Charge Level
RTC Module DS3231SN
Test Pads
Qwiic / Stemma QT
SPI ESD Protection Lines
External NOR Flash 64MB

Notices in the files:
parts and their libraries:
COPYRIGHT: Copyright (C) 2024 Ultra Librarian. All rights reserved.
